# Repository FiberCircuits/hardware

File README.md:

# hardware

This repository contains:

1) folders with [Kicad]([url](https://www.kicad.org/)) files (quick previews: [imu_fiber](https://kicanvas.org/?github=https://github.com/FiberCircuits/hardware/tree/main/imu_fiber/kicad_files) / [leds_fiber](https://kicanvas.org/?github=https://github.com/FiberCircuits/hardware/tree/main/leds_fiber/kicad_files)):

2) folders with embroidery and knitting design files:

(work in progress)

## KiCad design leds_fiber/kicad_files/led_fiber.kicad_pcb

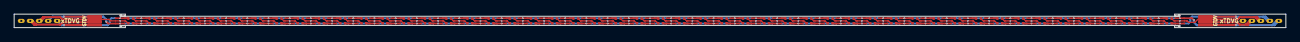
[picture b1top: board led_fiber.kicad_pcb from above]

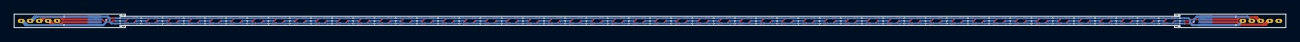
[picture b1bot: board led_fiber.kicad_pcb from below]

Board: 2 copper layers, 180.0 x 1.9 mm, 152 parts (51 on the bottom side), 4 nets.

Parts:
1, 2, 3, 4, 5, 6, 7, 8, 9, 10, 11, 12, 13, 14, 15, 16, 17, 18, 19, 20, 21, 22, 23, 24, 25, 26, 27, 28, 29, 30, 31, 32, 33, 34, 35, 36, 37, 38, 39, 40, 41, 42, 43, 44, 45, 46, 47, 48, 49, 50, 51, 52, 53, 54, 55, 56, 57, 58, 59, 60, 61, 62, 63, 64, 65, 66, 67, 68, 69, 70, 71, 72, 73, 74, 75, 76, 77, 78, 79, 80, 81, 82, 83, 84, 85, 86, 87, 88, 89, 90, 91, 92, 93, 94, 95, 96, 97, 98: Conn_PinHeader_1x03_P0.5mm_Horizontal_SMD
D1, D2, D3, D4, D5, D6, D7, D8, D9, D10, D11, D12, D13, D14, D15, D16, D17, D18, D19, D20, D21, D22, D23, D24, D25, D26, D27, D28, D29, D30, D31, D32, D33, D34, D35, D36, D37, D38, D39, D40, D41, D42, D43, D44, D45, D46, D47, D48, D49, D50: APA-104-1010; LED_APA-104-1010_1.0x1.0mm
J1, J1#2, J1#3, J1#4: pads; Conn_PinHeader_1.5mm_4pins_SMD

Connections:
/Din: 1.2, 2.2, 3.2, 4.2, 5.2, 6.2, 7.2, 8.2, 9.2, 10.2, 11.2, 12.2, 13.2, 14.2, 15.2, 16.2, 17.2, 18.2, 19.2, 20.2, 21.2, 22.2, 23.2, 24.2, 25.2, 26.2, 27.2, 28.2, 29.2, 30.2, 31.2, 32.2, 33.2, 34.2, 35.2, 36.2, 37.2, 38.2, 39.2, 40.2, 41.2, 42.2, 43.2, 44.2, 45.2, 46.2, 47.2, 48.2, 49.2, 50.2, 51.2, 52.2, 53.2, 54.2, 55.2, 56.2, 57.2, 58.2, 59.2, 60.2, 61.2, 62.2, 63.2, 64.2, 65.2, 66.2, 67.2, 68.2, 69.2, 70.2, 71.2, 72.2, 73.2, 74.2, 75.2, 76.2, 77.2, 78.2, 79.2, 80.2, 81.2, 82.2, 83.2, 84.2, 85.2, 86.2, 87.2, 88.2, 89.2, 90.2, 91.2, 92.2, 93.2, 94.2, 95.2, 96.2, 97.2, 98.2, D1.2 (DIN), D2.2 (DIN), D3.2 (DIN), D4.2 (DIN), D5.2 (DIN), D6.2 (DIN), D7.2 (DIN), D8.2 (DIN), D9.2 (DIN), D10.2 (DIN), D11.2 (DIN), D12.2 (DIN), D13.2 (DIN), D14.2 (DIN), D15.2 (DIN), D16.2 (DIN), D17.2 (DIN), D18.2 (DIN), D19.2 (DIN), D20.2 (DIN), D21.2 (DIN), D22.2 (DIN), D23.2 (DIN), D24.2 (DIN), D25.2 (DIN), D26.2 (DIN), D27.2 (DIN), D28.2 (DIN), D29.2 (DIN), D30.2 (DIN), D31.2 (DIN), D32.2 (DIN), D33.2 (DIN), D34.2 (DIN), D35.2 (DIN), D36.2 (DIN), D37.2 (DIN), D38.2 (DIN), D39.2 (DIN), D40.2 (DIN), D41.2 (DIN), D42.2 (DIN), D43.2 (DIN), D44.2 (DIN), D45.2 (DIN), D46.2 (DIN), D47.2 (DIN), D48.2 (DIN), D49.2 (DIN), D50.2 (DIN), J1.2, J1#2.2, J1#3.2, J1#4.2
/touch: J1.3, J1#2.3, J1#3.3, J1#4.3
GND: 1.1, 2.1, 3.1, 4.1, 5.1, 6.1, 7.1, 8.1, 9.1, 10.1, 11.1, 12.1, 13.1, 14.1, 15.1, 16.1, 17.1, 18.1, 19.1, 20.1, 21.1, 22.1, 23.1, 24.1, 25.1, 26.1, 27.1, 28.1, 29.1, 30.1, 31.1, 32.1, 33.1, 34.1, 35.1, 36.1, 37.1, 38.1, 39.1, 40.1, 41.1, 42.1, 43.1, 44.1, 45.1, 46.1, 47.1, 48.1, 49.1, 50.1, 51.1, 52.1, 53.1, 54.1, 55.1, 56.1, 57.1, 58.1, 59.1, 60.1, 61.1, 62.1, 63.1, 64.1, 65.1, 66.1, 67.1, 68.1, 69.1, 70.1, 71.1, 72.1, 73.1, 74.1, 75.1, 76.1, 77.1, 78.1, 79.1, 80.1, 81.1, 82.1, 83.1, 84.1, 85.1, 86.1, 87.1, 88.1, 89.1, 90.1, 91.1, 92.1, 93.1, 94.1, 95.1, 96.1, 97.1, 98.1, D1.1 (VSS), D2.1 (VSS), D3.1 (VSS), D4.1 (VSS), D5.1 (VSS), D6.1 (VSS), D7.1 (VSS), D8.1 (VSS), D9.1 (VSS), D10.1 (VSS), D11.1 (VSS), D12.1 (VSS), D13.1 (VSS), D14.1 (VSS), D15.1 (VSS), D16.1 (VSS), D17.1 (VSS), D18.1 (VSS), D19.1 (VSS), D20.1 (VSS), D21.1 (VSS), D22.1 (VSS), D23.1 (VSS), D24.1 (VSS), D25.1 (VSS), D26.1 (VSS), D27.1 (VSS), D28.1 (VSS), D29.1 (VSS), D30.1 (VSS), D31.1 (VSS), D32.1 (VSS), D33.1 (VSS), D34.1 (VSS), D35.1 (VSS), D36.1 (VSS), D37.1 (VSS), D38.1 (VSS), D39.1 (VSS), D40.1 (VSS), D41.1 (VSS), D42.1 (VSS), D43.1 (VSS), D44.1 (VSS), D45.1 (VSS), D46.1 (VSS), D47.1 (VSS), D48.1 (VSS), D49.1 (VSS), D50.1 (VSS), J1.4, J1#2.4, J1#3.4, J1#4.4
VCC: 1.3, 2.3, 3.3, 4.3, 5.3, 6.3, 7.3, 8.3, 9.3, 10.3, 11.3, 12.3, 13.3, 14.3, 15.3, 16.3, 17.3, 18.3, 19.3, 20.3, 21.3, 22.3, 23.3, 24.3, 25.3, 26.3, 27.3, 28.3, 29.3, 30.3, 31.3, 32.3, 33.3, 34.3, 35.3, 36.3, 37.3, 38.3, 39.3, 40.3, 41.3, 42.3, 43.3, 44.3, 45.3, 46.3, 47.3, 48.3, 49.3, 50.3, 51.3, 52.3, 53.3, 54.3, 55.3, 56.3, 57.3, 58.3, 59.3, 60.3, 61.3, 62.3, 63.3, 64.3, 65.3, 66.3, 67.3, 68.3, 69.3, 70.3, 71.3, 72.3, 73.3, 74.3, 75.3, 76.3, 77.3, 78.3, 79.3, 80.3, 81.3, 82.3, 83.3, 84.3, 85.3, 86.3, 87.3, 88.3, 89.3, 90.3, 91.3, 92.3, 93.3, 94.3, 95.3, 96.3, 97.3, 98.3, D1.3 (VDD), D2.3 (VDD), D3.3 (VDD), D4.3 (VDD), D5.3 (VDD), D6.3 (VDD), D7.3 (VDD), D8.3 (VDD), D9.3 (VDD), D10.3 (VDD), D11.3 (VDD), D12.3 (VDD), D13.3 (VDD), D14.3 (VDD), D15.3 (VDD), D16.3 (VDD), D17.3 (VDD), D18.3 (VDD), D19.3 (VDD), D20.3 (VDD), D21.3 (VDD), D22.3 (VDD), D23.3 (VDD), D24.3 (VDD), D25.3 (VDD), D26.3 (VDD), D27.3 (VDD), D28.3 (VDD), D29.3 (VDD), D30.3 (VDD), D31.3 (VDD), D32.3 (VDD), D33.3 (VDD), D34.3 (VDD), D35.3 (VDD), D36.3 (VDD), D37.3 (VDD), D38.3 (VDD), D39.3 (VDD), D40.3 (VDD), D41.3 (VDD), D42.3 (VDD), D43.3 (VDD), D44.3 (VDD), D45.3 (VDD), D46.3 (VDD), D47.3 (VDD), D48.3 (VDD), D49.3 (VDD), D50.3 (VDD), J1.1, J1#2.1, J1#3.1, J1#4.1

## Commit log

2023-10-01 Add licence.
2024-02-29 Add online KiCad previews.
